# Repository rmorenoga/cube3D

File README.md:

https://github.com/user-attachments/assets/da8bfa61-0a1e-48aa-958f-0410e7f2b091

# Smart Cellular Bricks for Decentralized Shape Classification and Damage Recovery

## System Requirements
### Hardware requirements
Training, simulation and plot generation are setup as a Python jupyter notebook **BIGCUBE_V2.ipynb**. We reccomend Google [colab](https://colab.research.google.com/) to run it. To open the notebook in colab you can either clone this repository and upload the notebook to Google colab, or create a fork of the repository and open it directly from github using Google colab. Most cells run on the free version of colab, however, for training you should use one of the paid plans as it uses resources over the free limits (12 GB of RAM).

Firmware compilation and communication with the cubes has been tested on a standard computer running Windows 10 or 11. See **Cube Firmware** below. 

The electronics folder contains the electronic designs necessary to build a cube in order to run the classification code in the robots. 

### Software requirements
Follow the instructions in the jupyter notebook to install the required Python packages and run the different cells. The notebook runs on the 2025.07 runtime version of colab (see more information [here](https://research.google.com/colaboratory/runtime-version-faq.html#2025.07)). Other Python packages required include (See **Install all required python packages** inside the notebook):
- keras==2.11.0
- tensorflow==2.12.0
- pygifsicle

and the **gifsicle** program which can be installed by calling in a cell:

	!sudo apt-get install gifsicle

Uploading the firmware to the cubes uses Python scripts, the requirements.txt in /OTAPython/ lists the necessary dependencies.
Getting data from the cubes requires installing [docker](docker.com/) in your system.

Both functions have been tested in a standard computer with Windows 11. See further details in each section below.

# Installation instructions 

Training and simulation are performed using python code organized in a jupyter notebook that runs preferably in Google colab **BIGCUBE_V2.ipynb**. To open it you can either clone this repository and upload the notebook to Google colab, or create a fork of the repository and open it directly from github using Google colab. The notebook also contains functions for exporting the model weights as a file for compiling the microcontroller code, tools for checking connections between real cubes and tools for generating graphs. For further instructions check the different cell descriptions inside the notebook. 

## Outputting neural network for firmware
To output the neural network to be uploaded to the firmware, run the corresponding cell in the jupyter notebook. It produces a text file that can be copied directly into the neural_network.h required by the firmware.

## Cube firmware
The cube firmware is saved in the 3DCubePlatformIO folder. You also need the neural_network.h file located in the root file of the repository. The following steps have been tested on Windows 10 and 11.

### Compiling
To be able to upload the firmware to the cubes it should first be compiled. The 3DCubePlatformIO folder is set up and configured as a [platformIO](platformio.org/) project. To make things easier we reccomend opening the folder with [visual studio code](https://code.visualstudio.com/). VSCode will automatically detect the platformio.ini file in the repository and ask you to install the platformIO extension. The extension will then automatically donwload all the required compilers and libraries. After installation press the compile button (check mark at the bottom left corner of VSCode). This will generate the firmware.bin file in the 3DCubePlatformIO/.pio/build/adafruit_metro_esp32s2/ subfolder. 

### Uploading
To upload the firmware.bin file first make sure the cubes are connected to the same local network. Then navigate to the OTApython folder and run the ESPuploadParallel.py script. This script should upload the firmware to all cubes connected in the network. To change the subnet that is scanned by the script, change the address ranges in lines 18, 80, 86, 52 and 53.

### Getting data from the cubes

After all cubes have been programmed. Turn them off, navigate to the StateReceivers folder in a terminal and launch the following command:

	docker compose up

 This will run the server configured in **docker-compose.yaml**. This requires that you have [docker](docker.com/) installed in your system and assumes that you have a [mongodb](mongodb.com/) installation with a **Test** database and a **Dummy** collection set up. Additionally make sure that the computer where you launch the server is on IP 192.168.72.22 and that you have firewall permissions to receive on TCP port 8000. You can change the server address in the firmware (/3DCubePlatformIO/src/3d_cube.ino) in line 688, this needs the cubes to be reprogrammed. After you launch the server, turn on the assembled cubes. The cubes will first perform the classification process, then connect to the network specified in lines 602 and 603 in the firmware (/3DCubePlatformIO/src/3d_cube.ino) and then post the data to the server.

After the data from all cubes arrive to the server, you can export the collection as a .json file.

## Electronics
This folder contains the electronic PCB designs necessary to fabricate a cube.

## Training Data:

The training data is downloaded from https://www.shapenet.org/ as ModelShapeNetCore, model_normalized.solid.binvox format. We use 7 classes: aircraft, boat, car, guitar, birdhouse(house), table and chair.

This data is then reduced by the function “training_data_cleaning.py”. Running this file will present you with scaled down versions of the downloaded training data. If you think the image is acceptable, close the image popup, and write “y” into the terminal. Else, write “n” in the terminal. The terminal will display how many successful images have been saved and also the number of voxels in each piece of data. Note: the data is expected to be in the file subfolder location vox_data/…. Cleaning the data is done one class at a time, and labels are saved simultaneously with the xdata. To change the class type, change line 129. 

The classification output should be as follows:

**N.  Class   Color**
- 0 **Plane** green  
- 1 **Chair** blue  
- 2 **Car** purple  
- 3 **Table** yellow 
- 4 **House** white  
- 5 **Guitar** pink  
- 6 **Boat** cyan
- **Damaged** red

The code will output two .npy files xdata and ydata that are ready to be inputted to the neural network training code. **Already cleaned data is stored in the xdata_7class.npy and ydata_7class.npy**

## Training for damage detection and recovery

Our code for damage detection and recovery can be found here: https://github.com/shyamsn97/cube-regen

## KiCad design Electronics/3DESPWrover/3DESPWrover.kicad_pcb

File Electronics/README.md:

# Electronic PCB design files

This folder contains the design files for fabricating the PCBs that make the sides of the cube and that enable processing, power and communication. Each folder contains a [Kicad](kicad.org/) project with both schematics and layout files. 

## 3DESPWrover 
This is the top PCB that contains an ESP32-WROOVER module, a DC-DC step down converter and a Neo-pixel RGB led. The BoardTest subfolder contains test code to check that all components are working properly in the board. This PCB contains a 14-way micromatch connector to connect this and the bottom PCB together. One top PCB is required for one cube.

## 3DESPWroverS
This is the side PCB. This PCB contains only communication and power headers as well as soldering connections to attach it to other similar PCBs and the bottom one. Four identical side PCBs are required for one cube.

## 3DESPWroverB
This is the bottom PCB. This PCB contains only communication and power headers as well as soldering connections to attach it to the side PCBs. This PCB contains a 14-way micromatch connector to connect this and the top PCB together. One bottom PCB is required for one cube.

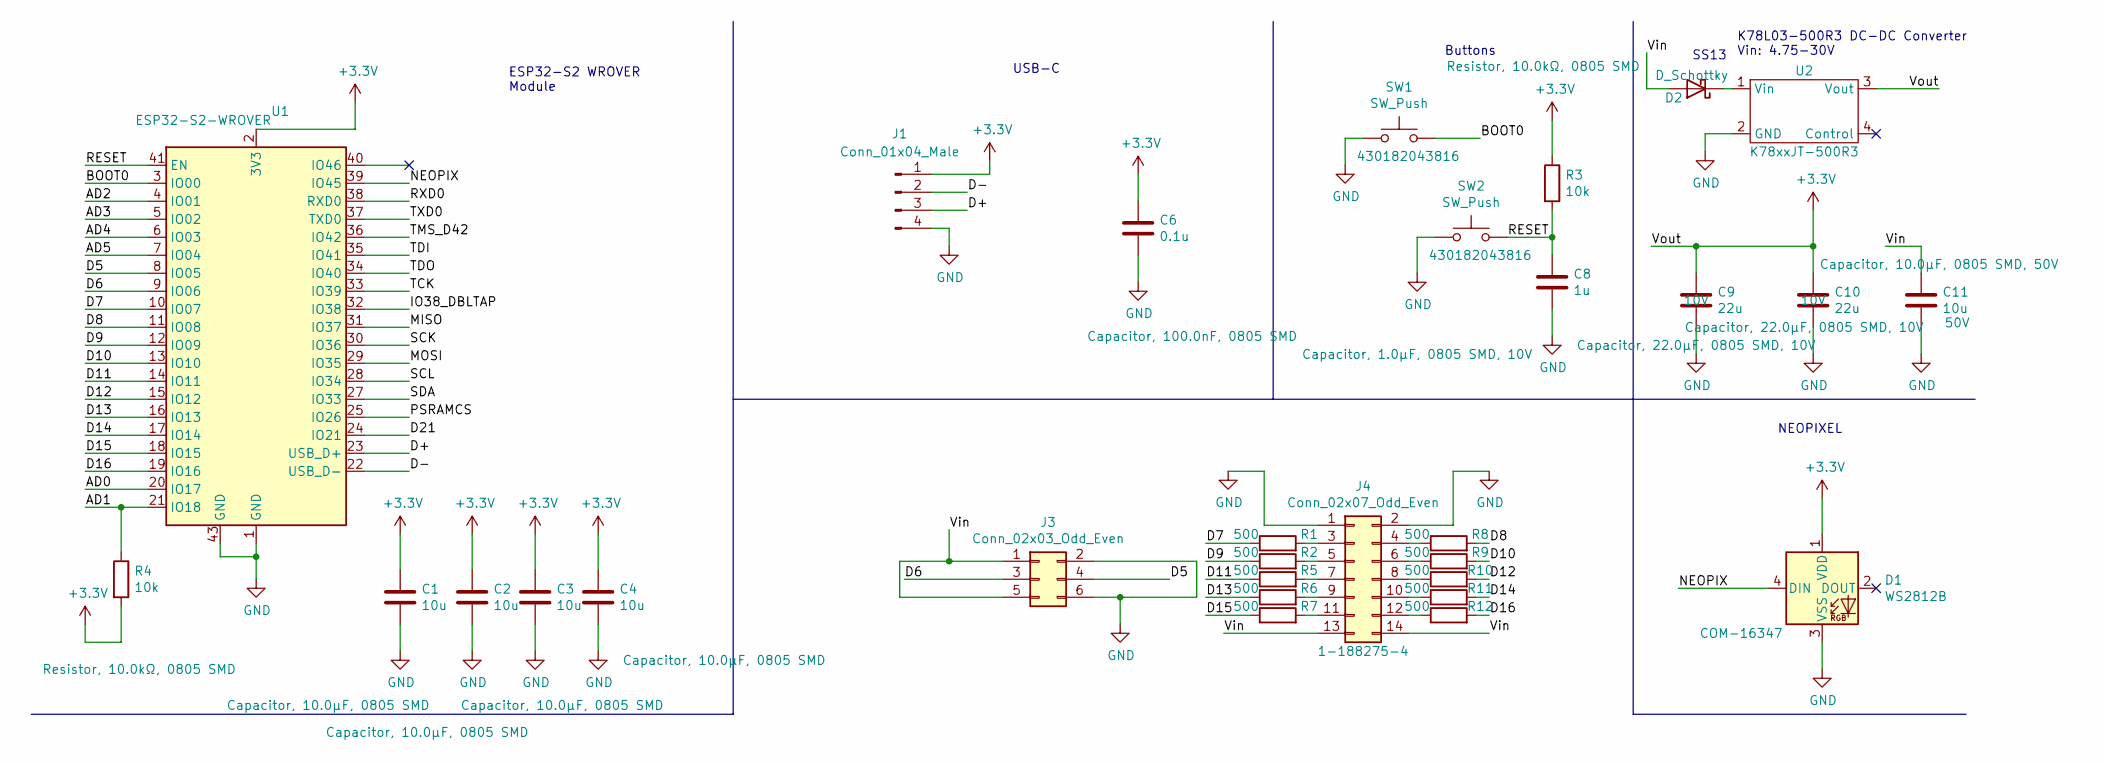
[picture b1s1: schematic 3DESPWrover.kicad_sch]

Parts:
C1, C2, C3, C4: 10u; C_0805_2012Metric_Pad1.18x1.45mm_HandSolder; MPN Capacitor, 10.0µF, 0805 SMD
C6: 0.1u; C_0805_2012Metric_Pad1.18x1.45mm_HandSolder; MPN Capacitor, 100.0nF, 0805 SMD
C8: 1u; C_0805_2012Metric_Pad1.18x1.45mm_HandSolder; MPN Capacitor, 1.0µF, 0805 SMD, 10V
C9, C10: 22u; C_0805_2012Metric_Pad1.18x1.45mm_HandSolder; Voltage 10V; MPN Capacitor, 22.0µF, 0805 SMD, 10V
C11: 10u; C_0805_2012Metric_Pad1.18x1.45mm_HandSolder; Voltage 50V; MPN Capacitor, 10.0µF, 0805 SMD, 50V
D1: WS2812B; LED_WS2812B_PLCC4_5.0x5.0mm_P3.2mm; MPN COM-16347
D2: D_Schottky; D_SMA; MPN SS13
J1: Conn_01x04_Male; PinHeader_1x04_P2.54mm_Vertical; MPN 0022052041
J3: Conn_02x03_Odd_Even; PinHeader_2x03_P2.54mm_Vertical; MPN SSW-103-01-F-D
J4: Conn_02x07_Odd_Even; TE_Micromatch_2,54_14_SMD; MPN 1-188275-4
R1, R2, R5, R6, R7, R8, R9, R10, R11, R12: 500; R_0603_1608Metric_Pad0.98x0.95mm_HandSolder; MPN Resistor, 510.0Ω, 0603 SMD
R3, R4: 10k; R_0805_2012Metric_Pad1.20x1.40mm_HandSolder; MPN Resistor, 10.0kΩ, 0805 SMD
SW1, SW2: SW_Push; SW_SPST_B3S-1000; MPN 430182043816
U1: ESP32-S2-WROVER; MPN DFR0743-WROVER
U2: K78xxJT-500R3; K7803JT-500R3-SMD; MPN K7803JT-500R3

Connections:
+3V3: C1.1, C2.1, C3.1, C4.1, C6.1, C9.1, C10.1, D1.1 (VDD), J1.1, R3.1, R4.2, U1.2 (3V3), U2.3 (Vout)
/AD0: U1.20 (IO17)
/AD1: R4.1, U1.21 (IO18)
/AD2: U1.4 (IO01)
/AD3: U1.5 (IO02)
/AD4: U1.6 (IO03)
/AD5: U1.7 (IO04)
/BOOT0: SW1.2, U1.3 (IO00)
/D5: J3.4, U1.8 (IO05)
/D6: J3.3, U1.9 (IO06)
/D7: R1.1, U1.10 (IO07)
/D8: R8.2, U1.11 (IO08)
/D9: R2.1, U1.12 (IO09)
/D10: R9.2, U1.13 (IO10)
/D11: R5.1, U1.14 (IO11)
/D12: R10.2, U1.15 (IO12)
/D13: R6.1, U1.16 (IO13)
/D14: R11.2, U1.17 (IO14)
/D15: R7.1, U1.18 (IO15)
/D16: R12.2, U1.19 (IO16)
/D21: U1.24 (IO21)
/D+: J1.3, U1.23 (USB_D+)
/D-: J1.2, U1.22 (USB_D-)
/IO38_DBLTAP: U1.32 (IO38)
/MISO: U1.31 (IO37)
/MOSI: U1.29 (IO35)
/NEOPIX: D1.4 (DIN), U1.39 (IO45)
/PSRAMCS: U1.25 (IO26)
/RESET: C8.1, R3.2, SW2.2, U1.41 (EN)
/RXD0: U1.38 (RXD0)
/SCK: U1.30 (IO36)
/SCL: U1.28 (IO34)
/SDA: U1.27 (IO33)
/TCK: U1.33 (IO39)
/TDI: U1.35 (IO41)
/TDO: U1.34 (IO40)
/TMS_D42: U1.36 (IO42)
/TXD0: U1.37 (TXD0)
/Vin: C11.1, D2.2 (A), J3.1, J3.5, J4.13, J4.14
GND: C1.2, C2.2, C3.2, C4.2, C6.2, C8.2, C9.2, C10.2, C11.2, D1.3 (VSS), J1.4, J3.2, J3.6, J4.1, J4.2, SW1.1, SW2.1, U1.1 (GND), U1.26 (GND), U1.42 (GND), U1.43 (GND), U1.44 (GND), U1.45 (GND), U1.46 (GND), U1.47 (GND), U1.48 (GND), U1.49 (GND), U1.50 (GND), U1.51 (GND), U2.2 (GND)
unnamed: D2.1 (K), U2.1 (Vin)
unnamed: J4.3, R1.2
unnamed: J4.4, R8.1
unnamed: J4.5, R2.2
unnamed: J4.6, R9.1
unnamed: J4.7, R5.2
unnamed: J4.8, R10.1
unnamed: J4.9, R6.2
unnamed: J4.10, R11.1
unnamed: J4.11, R7.2
unnamed: J4.12, R12.1

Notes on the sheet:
Buttons
K78L03-500R3 DC-DC Converter Vin: 4.75-30V
NEOPIXEL
ESP32-S2 WROVER Module
USB-C
SS13

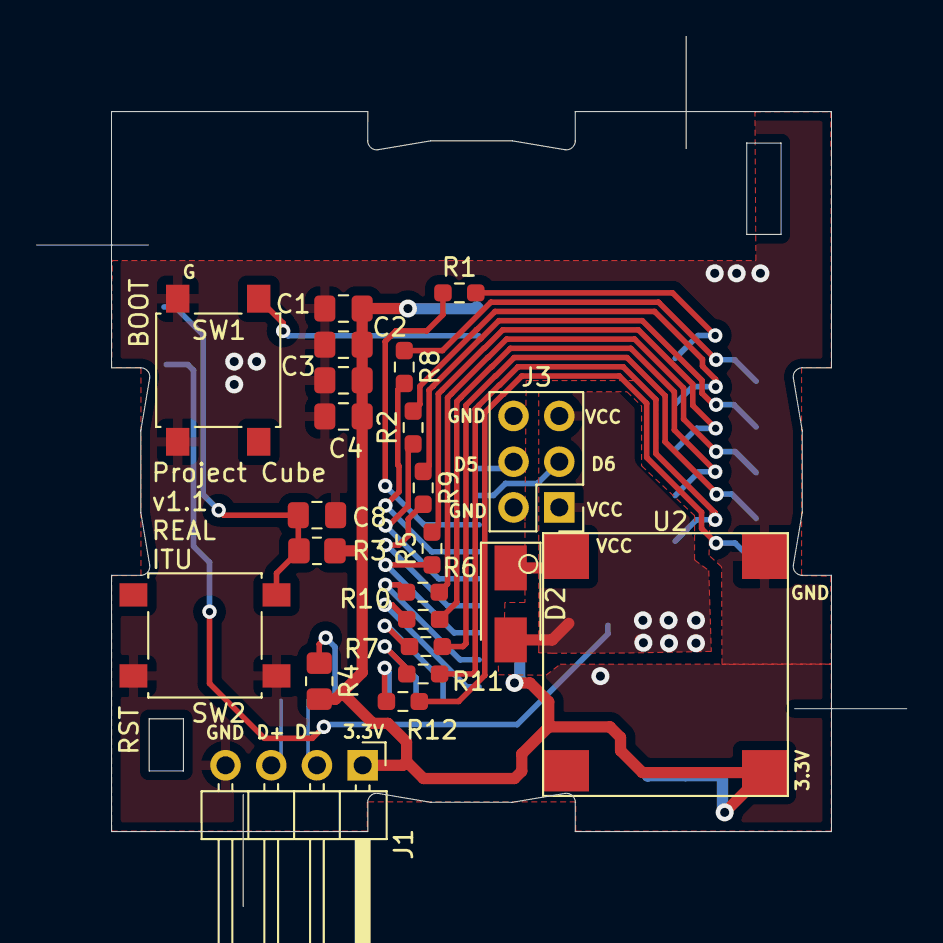
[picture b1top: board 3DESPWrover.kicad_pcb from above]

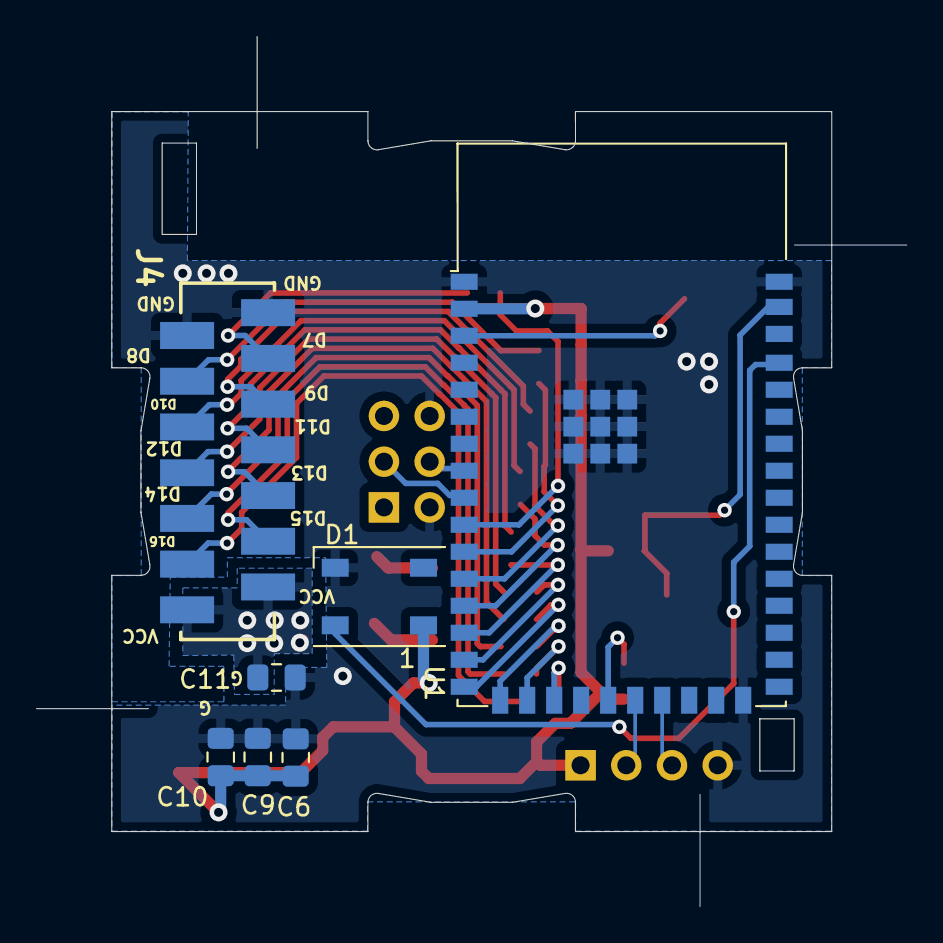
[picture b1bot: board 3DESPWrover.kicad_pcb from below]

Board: 2 copper layers, 40.0 x 40.0 mm, 30 parts (7 on the bottom side), 32 nets.

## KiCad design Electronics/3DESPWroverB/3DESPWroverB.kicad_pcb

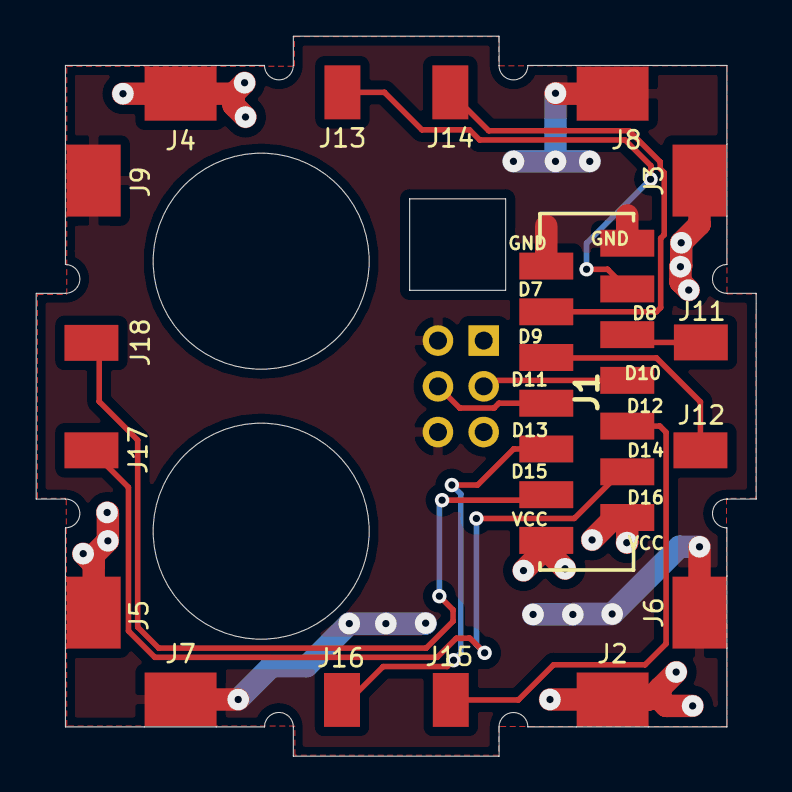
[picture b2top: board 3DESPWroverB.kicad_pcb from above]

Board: 2 copper layers, 40.0 x 40.0 mm, 18 parts (1 on the bottom side), 12 nets.

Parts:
J1: Conn_02x07_Odd_Even; TE_Micromatch_2,54_14_SMD
J2, J3, J4, J5, J6, J7, J8, J9: Conn_01x01; CubeSidePad
J10: Conn_02x03_Odd_Even; PinHeader_2x03_P2.54mm_Vertical
J11, J12, J13, J14, J15, J16, J17, J18: Conn_01x01; CubeCenterPad

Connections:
/D7: J1.3, J13.1
/D8: J1.4, J14.1
/D9: J1.5, J11.1
/D10: J1.6, J12.1
/D11: J1.7, J10.3
/D12: J1.8, J10.4
/D13: J1.9, J15.1
/D14: J1.10, J16.1
/D15: J1.11, J17.1
/D16: J1.12, J18.1
GND: J1.1, J1.2, J6.1, J7.1, J8.1, J9.1, J10.2, J10.6
VCC: J1.13, J1.14, J2.1, J3.1, J4.1, J5.1, J10.1, J10.5

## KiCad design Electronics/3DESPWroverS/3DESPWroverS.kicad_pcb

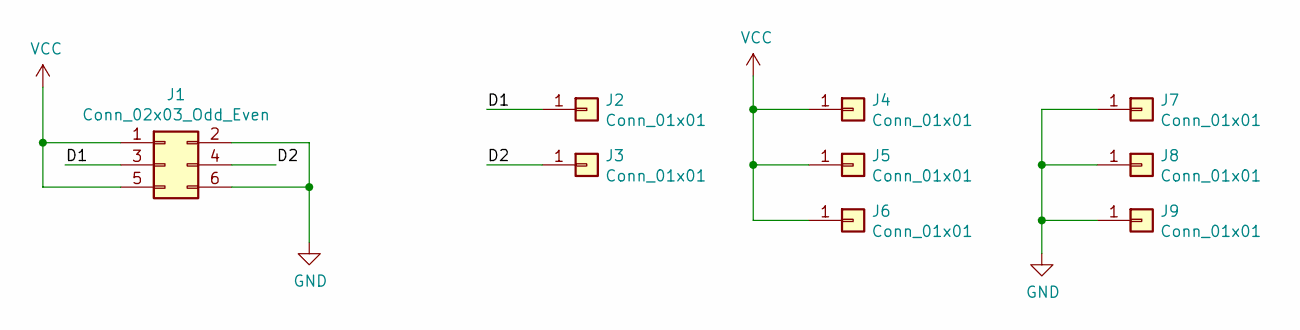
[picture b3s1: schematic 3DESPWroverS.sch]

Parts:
J1: Conn_02x03_Odd_Even; PinHeader_2x03_P2.54mm_Vertical
J2, J3: Conn_01x01; CubeCenterPad
J4, J5, J6, J7, J8, J9: Conn_01x01; CubeSidePad

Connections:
/D1: J1.3, J2.1
/D2: J1.4, J3.1
GND: J1.2, J1.6, J7.1, J8.1, J9.1
VCC: J1.1, J1.5, J4.1, J5.1, J6.1

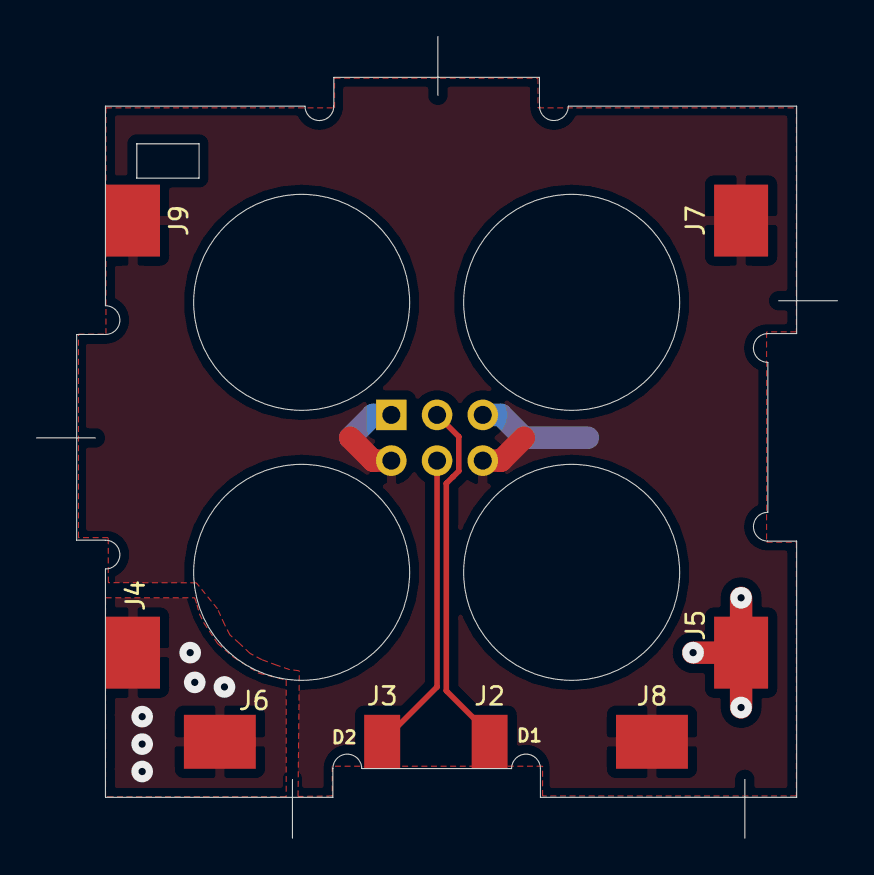
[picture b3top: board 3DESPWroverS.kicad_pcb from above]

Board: 2 copper layers, 40.0 x 40.0 mm, 9 parts (1 on the bottom side), 4 nets.

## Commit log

2025-10-25 Updated in colab
2025-10-25 Updated using Colab
2025-10-25 Cleaned readme
2025-10-25 Added electronic designs
2025-10-26 Tuned some parameters to create all graphs without errors
2025-10-28 Updated Readme to include video and hardware and software requirements
2025-10-28 Formatting code, and correcting banner
2026-04-05 added code to save hardware experiments shapes from the failure rate experiment (shapes without the damaged cubes in them) to a variable to compare them with the base line in the future
2026-04-05 Added baseline alg for comparison: Weisfeiler–Lehman (WL) kernel + linear SVM
2026-04-05 Added code to read out of distribution shapes and modified the code to reconstruct the shapes to allow a that targetShape could be None
2026-04-05 Fixed bug in reconstructing shape from get neighbors if the target shape was not given
2026-04-05 Baseline accuracy results in real conditions (taking into account unconnected groups of cells due to damaged cells). Thus, the baseline is applied to each of the connected groups of cells and the per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
2026-04-07 Added small boat shape to out of distribution shapes
2026-04-07 Added test neighbors and shape classification results for table 372 with damage
2026-04-08 Rename testNeighbors_Table_372_1727276067.4498246.csv to testNeighbors_Table_372_NoDamage1727276067.4498246.csv
2026-04-08 Fixed code to find the correct get neighbours file (without damage) in hardware failure rate experiments
2026-04-08 Move testNeighbors_Table_372_Damage CSV to Damaged folder
2026-04-08 Rename Experiment data/hardware/Table_372/ShapeClass_Table_372_Damage_Test1.json to Experiment data/hardware/Table_372/Damaged/ShapeClass_Table_372_Damage_Test1.json
2026-04-08 Rename Experiment data/hardware/Table_372/ShapeClass_Table_372_Damage_Test2.json to Experiment data/hardware/Table_372/Damaged/ShapeClass_Table_372_Damage_Test2.json
2026-04-08 Rename Experiment data/hardware/Table_372/ShapeClass_Table_372_Damage_Test3.json to Experiment data/hardware/Table_372/Damaged/ShapeClass_Table_372_Damage_Test3.json
2026-04-08 Finished reorganization. Now, the damaged table experiment is stored in its own folder and we can remove the ad-hoc code to find the right get neighbors file
2026-04-08 restored deleted files of table with damages
2026-04-08 Added code to study performance on bigger and smaller shapes of the dataset
2026-04-08 Added code to save results of scaled shapes (out of distribution) to a Google drive to plot results later
2026-04-09 Added local hash in addittion of a global feature to estimate properties of the WL alg.
2026-04-09 Added testneighbors damaged boat 144
2026-04-09 Added tests for damaged boat 144
2026-04-09 Added code to calculate time to result and better graphs of scaled shapes
2026-04-10 Added new test neighbors to table 372 damage
2026-04-14 Added plots comparing WL vs NCA against the failure rate
2026-04-14 Added aggregated data for convergence speed
2026-04-16 Improved documentation
2026-05-11 Moved files around to clean the repository
2026-05-11 Removed .vscode files
2026-05-11 Removed pycache
2026-05-13 Updated shape data paths
2026-05-14 Changed the format of the graphs to make them homogeneous
2026-05-15 modified graph of time to result to homogenize format
2026-05-24 added code to create source data for figshare
2026-05-25 removed outputs
